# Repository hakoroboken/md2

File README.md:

# MD2

## 部品リスト

| 型番           | 部品名                                                   | 個数 |
|---------------|-----------------------------------------------------------|------|
| 0.1u          | コンデンサ (0.1u)                                       | 12   |
| 10k           | 抵抗 (10k)                                               | 10   |
| SW_Push       | プッシュスイッチ (SW_Push)                               | 8    |
| 1u            | コンデンサ (1u)                                          | 6    |
| XT30PW-M      | XT30PWM                                                   | 5    |
| Conn_01x03_Pin| コネクタ (1x03ピン)                                      | 4    |
| TB6643KQ      | モータードライバー (TB6643KQ)                             | 4    |
| Conn_01x02_Pin| コネクタ (1x02ピン)                                      | 2    |
| TC74HC4066AP_F| パッケージ (DIP-14)                                      | 4.45 |
| SeeeduinoXIAO | Seeeduino XIAO                                            | 1    |
| NJM7805FA     | パッケージ (TO-220F-3)                                    | 1    |
| SW_Push       | バッテリーソース (SW_Push)                               | 1    |
| 1k            | 抵抗 (1k)                                                 | 1    |
| R             | 抵抗                                                      | 1    |
| Conn_01x01_Pin| LED接続 (led_conn)                                       | 1    |
| TC74HC04AP    | パッケージ (DIP-14)                                      | 4.45 |
| LED           | LED                                                       | 1    |

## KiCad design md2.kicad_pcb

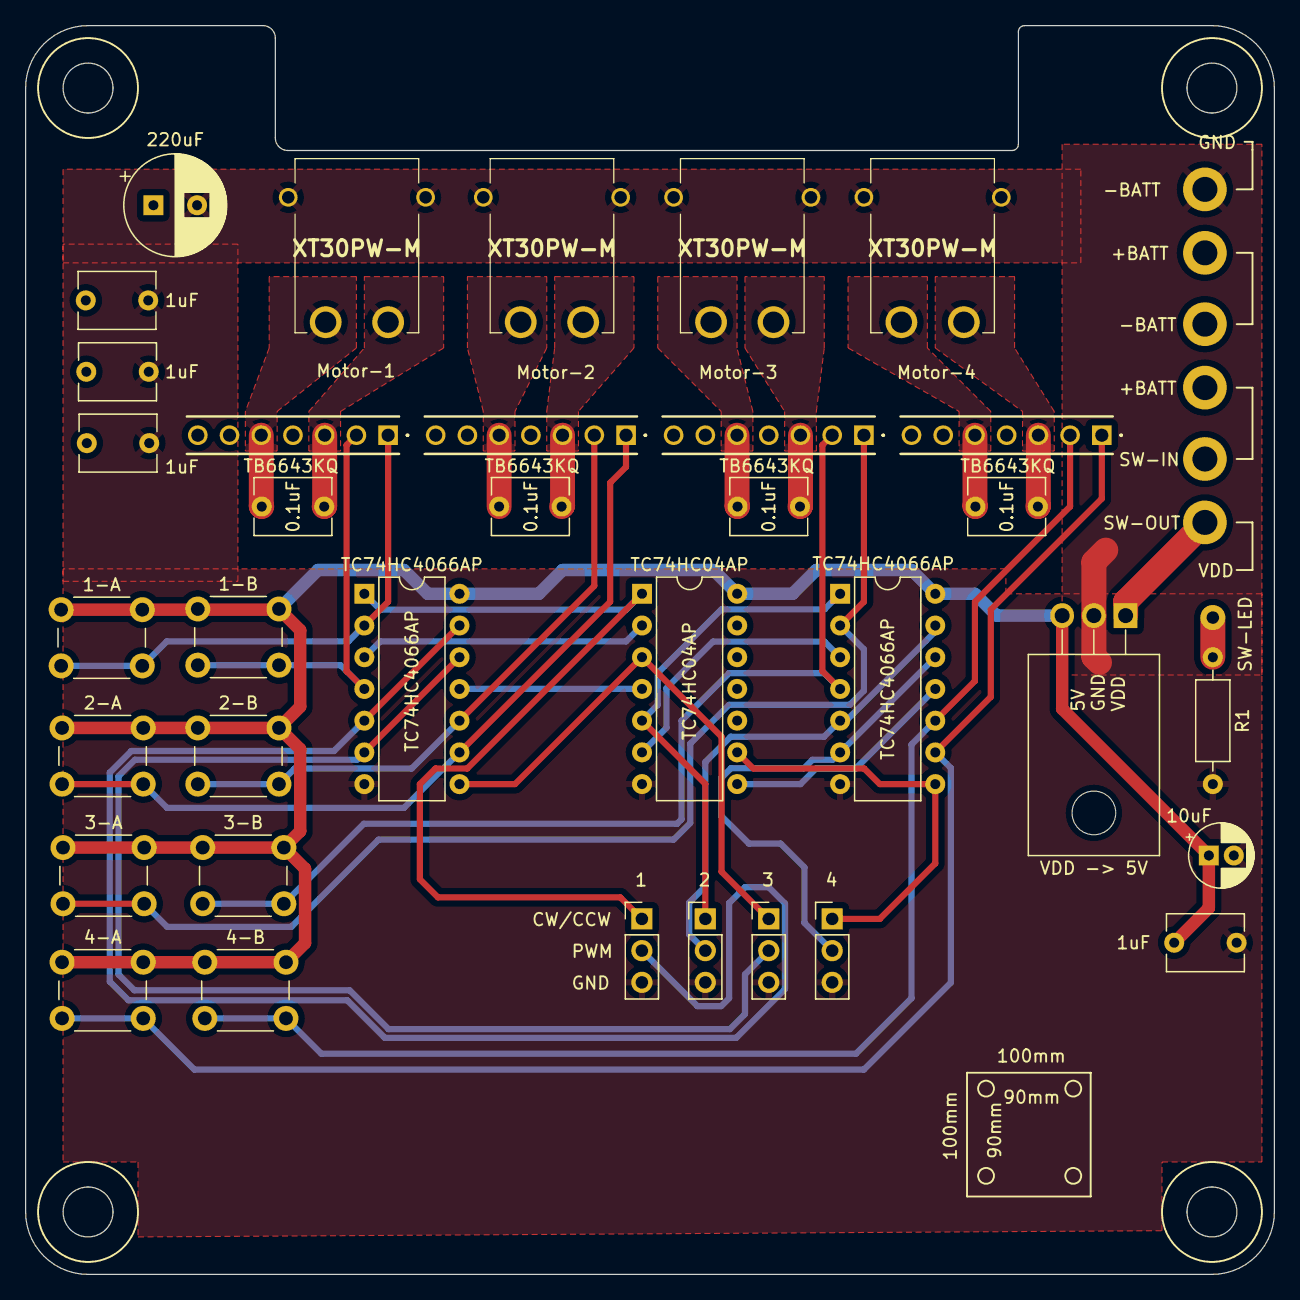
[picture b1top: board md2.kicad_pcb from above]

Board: 2 copper layers, 100.0 x 100.0 mm, 39 parts (0 on the bottom side), 34 nets.

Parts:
0.1uF, 0.1uF#2, 0.1uF#3, 0.1uF#4: 0.1u; C_Disc_D6.0mm_W4.4mm_P5.00mm
1-A, 1-B, 2-A, 2-B, 3-A, 3-B, 4-A, 4-B: SW_Push; SW_PUSH_6mm
1uF, 1uF#2, 1uF#3, 1uF#4: 1u; C_Disc_D6.0mm_W4.4mm_P5.00mm
10uF: 10u; CP_Radial_D5.0mm_P2.00mm
220uF: 220u; CP_Radial_D8.0mm_P3.50mm
IC4, IC5, IC6: TB6643KQ
J1, J2, J3, J4: Conn_01x03_Pin; PinHeader_1x03_P2.54mm_Vertical
J9, J10: Conn_01x02_Pin; batterySoruce
J11: Conn_01x01_Pin; led_conn
R1: R; R_Axial_DIN0207_L6.3mm_D2.5mm_P10.16mm_Horizontal
SW9: SW_Push; batterySoruce
TB6643KQ: TB6643KQ
TC74HC04AP: TC74HC04AP; DIP-14_W7.62mm
TC74HC4066AP, TC74HC4066AP#2: TC74HC4066AP_F_; DIP-14_W7.62mm
VDD -> 5V: NJM7805FA; TO-220F-3_Horizontal_TabDown
XT30PW-M, XT30PW-M#2, XT30PW-M#3, XT30PW-M#4: XT30PW-M; XT30PWM

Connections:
+5V: 1-A.1, 1-B.1, 1uF.1, 2-A.1, 2-B.1, 3-A.1, 3-B.1, 4-A.1, 4-B.1, 10uF.1, TC74HC04AP.14 (VCC), TC74HC4066AP.14 (VCC), TC74HC4066AP#2.14 (VCC), VDD -> 5V.3 (VOUT)
+BATT: J9.1, SW9.1
CW/CCW-1: J1.1, TC74HC04AP.1 (1A), TC74HC4066AP.1 (1I/O)
CW/CCW-2: J3.1, TC74HC04AP.3 (2A), TC74HC4066AP.8 (3I/O)
CW/CCW-3: J2.1, TC74HC04AP.5 (3A), TC74HC4066AP#2.1 (1I/O)
CW/CCW-4: J4.1, TC74HC04AP.9 (4A), TC74HC4066AP#2.8 (3I/O)
GND: 1uF.2, 1uF#2.2, 1uF#3.2, 1uF#4.2, 10uF.2, 220uF.2, IC4.4 (GND), IC5.4 (GND), IC6.4 (GND), J1.3, J2.3, J3.3, J4.3, J10.2, R1.2, TB6643KQ.4 (GND), TC74HC04AP.7 (GND), TC74HC4066AP.7 (GND_(VSS)), TC74HC4066AP#2.7 (GND_(VSS)), VDD -> 5V.2 (GND), XT30PW-M.3, XT30PW-M.4, XT30PW-M#2.3, XT30PW-M#2.4, XT30PW-M#3.3, XT30PW-M#3.4, XT30PW-M#4.3, XT30PW-M#4.4
MD-1-1: 1-A.2, IC4.1 (IN1), TC74HC4066AP.2 (1O/I)
MD-1-2: 1-B.2, IC4.2 (IN2), TC74HC4066AP.4 (2I/O)
MD-2-1: 2-A.2, IC5.1 (IN1), TC74HC4066AP.9 (3O/I)
MD-2-2: 2-B.2, IC5.2 (IN2), TC74HC4066AP.10 (4O/I)
MD-3-1: 3-A.2, IC6.1 (IN1), TC74HC4066AP#2.2 (1O/I)
MD-3-2: 3-B.2, IC6.2 (IN2), TC74HC4066AP#2.4 (2I/O)
MD-4-1: 4-A.2, TB6643KQ.1 (IN1), TC74HC4066AP#2.9 (3O/I)
MD-4-2: 4-B.2, TB6643KQ.2 (IN2), TC74HC4066AP#2.10 (4O/I)
unnamed: 0.1uF#4.1, IC4.3 (OUT1), XT30PW-M.2
unnamed: 0.1uF#4.2, IC4.5 (OUT2), XT30PW-M.1
unnamed: 0.1uF#2.1, IC5.3 (OUT1), XT30PW-M#2.2
unnamed: 0.1uF#2.2, IC5.5 (OUT2), XT30PW-M#2.1
unnamed: 0.1uF.1, IC6.3 (OUT1), XT30PW-M#4.2
unnamed: 0.1uF.2, IC6.5 (OUT2), XT30PW-M#4.1
unnamed: 0.1uF#3.1, TB6643KQ.3 (OUT1), XT30PW-M#3.2
unnamed: 0.1uF#3.2, TB6643KQ.5 (OUT2), XT30PW-M#3.1
unnamed: J9.2, J10.1
unnamed: J11.1, R1.1
PWM-1: J1.2, TC74HC4066AP.5 (2C), TC74HC4066AP.13 (1C)
PWM-2: J3.2, TC74HC4066AP.6 (3C), TC74HC4066AP.12 (4C)
PWM-3: J2.2, TC74HC4066AP#2.5 (2C), TC74HC4066AP#2.13 (1C)
PWM-4: J4.2, TC74HC4066AP#2.6 (3C), TC74HC4066AP#2.12 (4C)
VDD: 1uF#2.1, 1uF#3.1, 1uF#4.1, 220uF.1, IC4.7 (VM), IC5.7 (VM), IC6.7 (VM), SW9.2, TB6643KQ.7 (VM), VDD -> 5V.1 (VIN)
r-CW/CCW-1: TC74HC04AP.2 (1Y), TC74HC4066AP.3 (2O/I)
r-CW/CCW-2: TC74HC04AP.4 (2Y), TC74HC4066AP.11 (4I/O)
r-CW/CCW-3: TC74HC04AP.6 (3Y), TC74HC4066AP#2.3 (2O/I)
r-CW/CCW-4: TC74HC04AP.8 (4Y), TC74HC4066AP#2.11 (4I/O)

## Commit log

2024-01-13 Create LICENCE
2024-07-10 support survo motor
